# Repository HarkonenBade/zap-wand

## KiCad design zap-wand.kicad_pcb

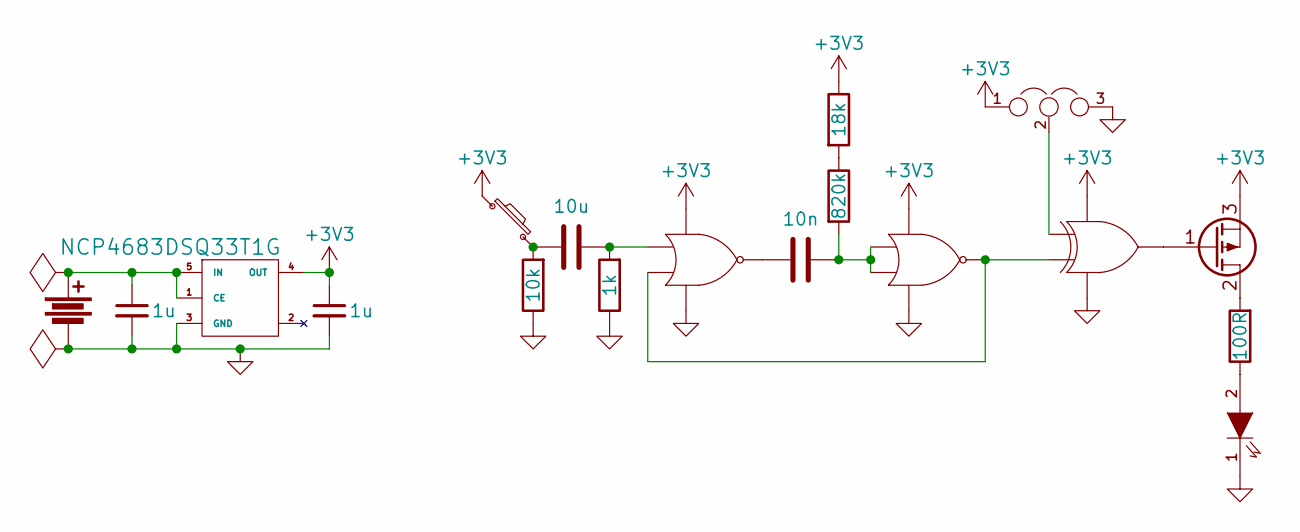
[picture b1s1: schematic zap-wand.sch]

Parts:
BATT1: Battery; SIL-254P-02
C1: 10u; 0603; Farnell 2494233
C2: 10n; 0805; Farnell 2470490
C3, C4: 1u; 0603; Farnell 2362099
D1: LED; SIL-254P-02
IC1: NC7WZ02; US8-3.1mm; Farnell 2453144
IC2: NC7SZ86; SC-70-5; Farnell 1652016
JP1: JUMPER3; solder_jumper_3
Q1: Q_PMOS_GDS; SOT-323; Farnell 2069551
R1: 1k; 0603; Farnell 9330380
R2: 820k; 0603; Farnell 9331581
R3: 100R; 0603; Farnell 2447227
R4: 10k; 0603; Farnell 9330399
R5: 18k; 0603; Farnell 9330720
SW1: SW_PUSH_SMALL; FSM10JH; Farnell 1555986
U1: NCP4683DSQ33T1G; SC-70-5; Farnell 2464280

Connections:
+3V3: C4.1, IC1.8 (VCC), IC2.5 (VCC), JP1.1, Q1.3 (S), R5.1, SW1.1, U1.4 (OUT)
GND: BATT1.2, C3.2, C4.2, D1.1 (K), IC1.4 (GND), IC2.3 (GND), JP1.3, R1.1, R4.1, U1.3 (GND)
unnamed: BATT1.1, C3.1, U1.1 (CE), U1.5 (IN)
unnamed: C1.1, IC1.1 (A1), R1.2
unnamed: C1.2, R4.2, SW1.2
unnamed: C2.1, IC1.5 (A2), IC1.6 (B2), R2.2
unnamed: C2.2, IC1.7 (Y1)
unnamed: D1.2 (A), R3.1
unnamed: IC1.2 (B1), IC1.3 (Y2), IC2.2 (B)
unnamed: IC2.1 (A), JP1.2
unnamed: IC2.4 (Y), Q1.1 (G)
unnamed: Q1.2 (D), R3.2
unnamed: R2.1, R5.2

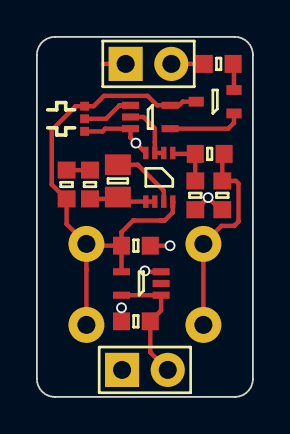
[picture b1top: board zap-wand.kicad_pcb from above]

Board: 2 copper layers, 12.0 x 20.0 mm, 17 parts (1 on the bottom side), 13 nets.

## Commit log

2016-07-17 Base design
2016-07-18 Various bits
2016-07-19 Various tweaks and fixes
2016-07-21 Beefier regulator, pcb shuffle
2016-07-21 Gerbils
2016-07-22 Added xor output inverter
